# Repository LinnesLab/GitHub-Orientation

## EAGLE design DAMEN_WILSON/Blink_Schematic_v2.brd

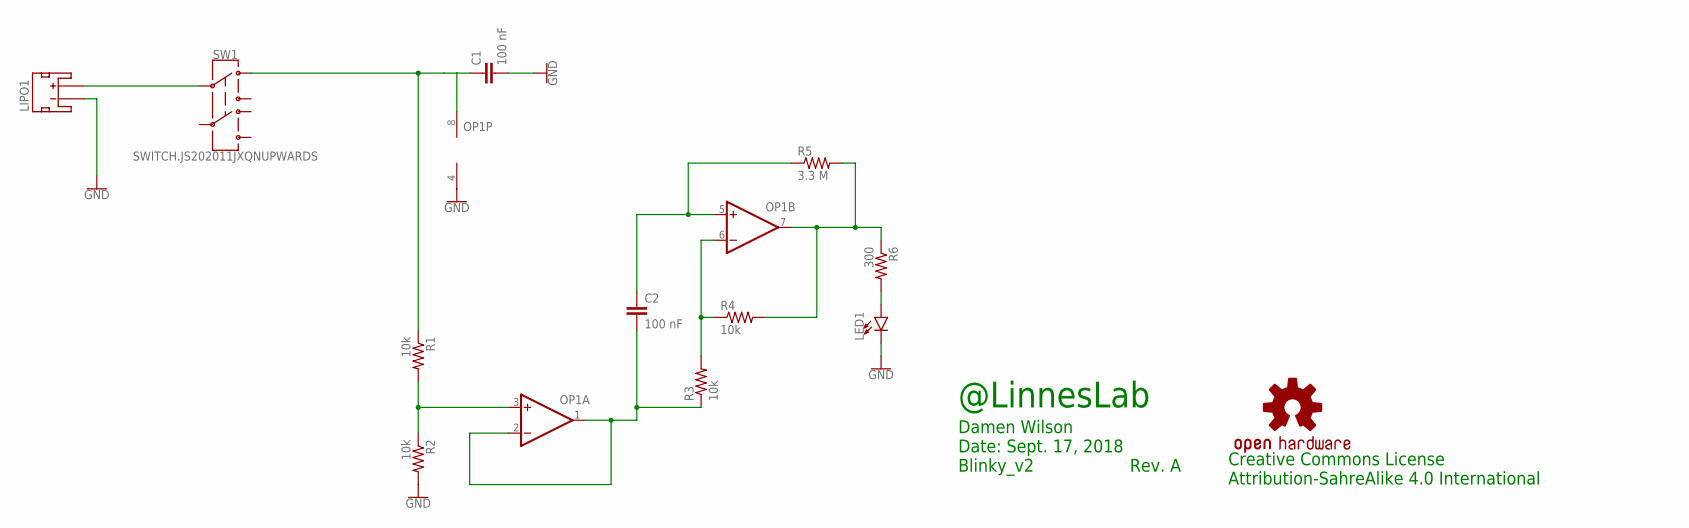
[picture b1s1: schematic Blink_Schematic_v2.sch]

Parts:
C1, C2: 100 nF; C0402
LED1: LED0603; LED-0603
LIPO1: JST_2MM_MALE; JST-2-SMD
LOGO1: OSHW-LOGOL; OSHW-LOGO-L
OP1: OP-DUALRM; MSOP08
R1, R2, R3, R4: 10k; R0402
R5: 3.3 M; R0402
R6: 300; R0402
SW1: SWITCH.JS202011JXQNUPWARDS; SWITCH.00

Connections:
GND: C1.2, LED1.C, LIPO1.1 (-), OP1.4 (V-), R2.2
unnamed: LIPO1.2 (+), SW1.2
unnamed: C1.1, OP1.8 (V+), R1.1, SW1.1
unnamed: OP1.3 (+IN), R1.2, R2.1
unnamed: C2.2, OP1.1 (OUT), OP1.2 (-IN), R3.1
unnamed: C2.1, OP1.5 (+IN), R5.1
unnamed: OP1.6 (-IN), R3.2, R4.1
unnamed: OP1.7 (OUT), R4.2, R5.2, R6.1
unnamed: LED1.A, R6.2

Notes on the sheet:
@LinnesLab
Damen Wilson Date: Sept. 17, 2018 Blinky_v2 Rev. A
Creative Commons License Attribution-SahreAlike 4.0 International

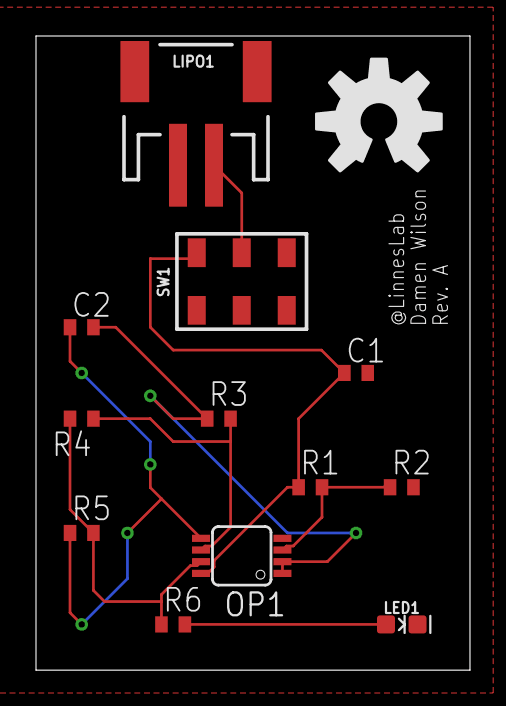
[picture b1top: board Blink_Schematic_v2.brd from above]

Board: 2 copper layers, 24.1 x 35.2 mm, 13 parts (0 on the bottom side), 9 nets.

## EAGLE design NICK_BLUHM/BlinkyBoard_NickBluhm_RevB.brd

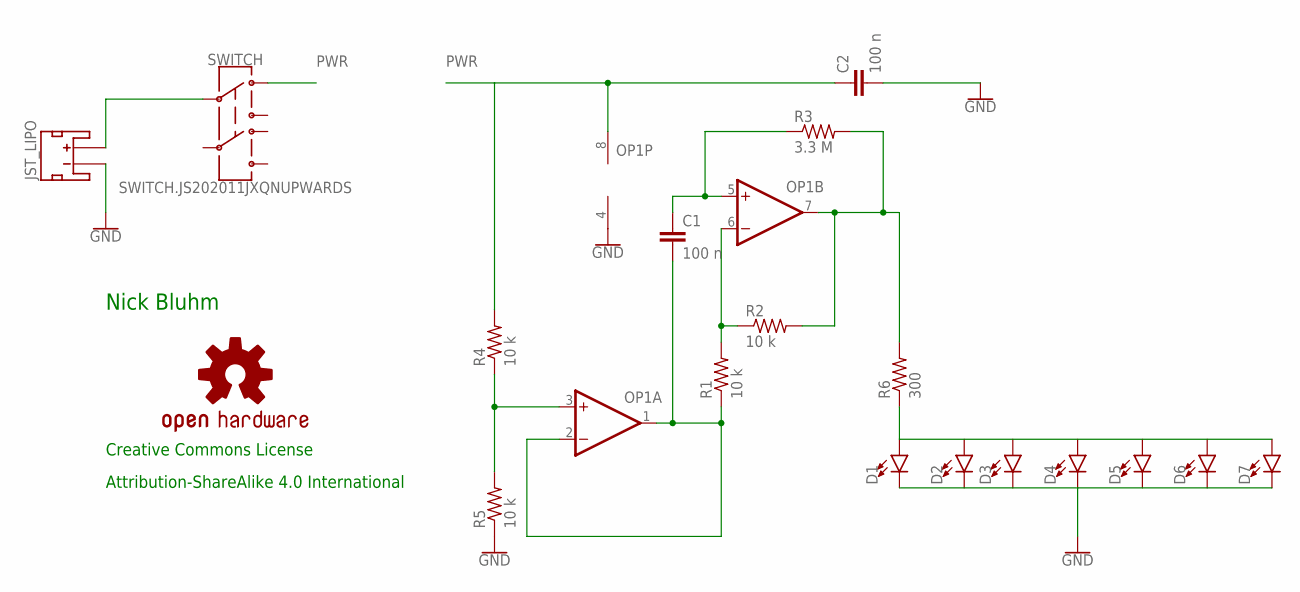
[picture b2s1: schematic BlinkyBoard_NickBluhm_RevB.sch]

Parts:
C1, C2: 100 n; C0402
D1, D2, D3, D4, D5, D6, D7: LED0603; LED-0603
JST_LIPO: 3.7 V; JST-2-SMD
LOGO1: OSHW-LOGOL-COPPER; OSHW-LOGO-L_COPPER
OP1: OP-DUALRM; MSOP08
R1, R2, R4, R5: 10 k; R0402
R3: 3.3 M; R0402
R6: 300; R0402
SWITCH: SWITCH.JS202011JXQNUPWARDS; SWITCH.00
U$5: LINNES.LAB.LOGO

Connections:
GND: C2.2, D1.C, D7.C, JST_LIPO.1 (-), OP1.4 (V-), R5.1
unnamed: JST_LIPO.2 (+), SWITCH.2
unnamed: OP1.3 (+IN), R4.1, R5.2
unnamed: C1.2, OP1.1 (OUT), OP1.2 (-IN), R1.1
unnamed: OP1.6 (-IN), R1.2, R2.1
unnamed: C1.1, OP1.5 (+IN), R3.1
unnamed: OP1.7 (OUT), R2.2, R3.2, R6.2
unnamed: D1.A, D7.A, R6.1
PWR: C2.1, OP1.8 (V+), R4.2, SWITCH.1

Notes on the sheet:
Nick Bluhm
Creative Commons License
Attribution-ShareAlike 4.0 International

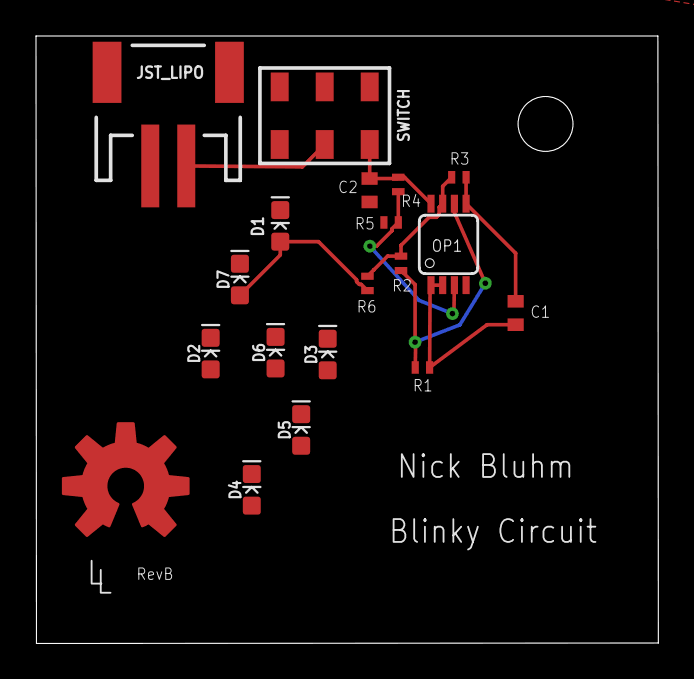
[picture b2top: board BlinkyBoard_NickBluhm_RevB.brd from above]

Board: 2 copper layers, 34.6 x 33.7 mm, 20 parts (0 on the bottom side), 9 nets.

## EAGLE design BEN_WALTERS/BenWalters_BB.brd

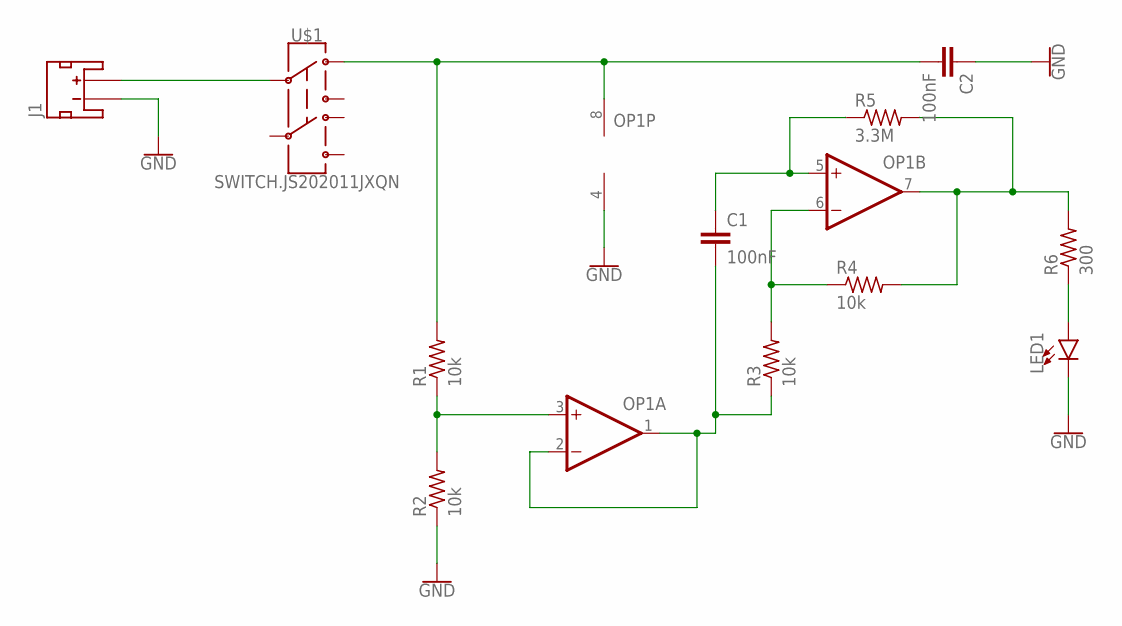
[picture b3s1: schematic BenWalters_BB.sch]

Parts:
C1, C2: 100nF; C0805
J1: 3.7V; JST-2-SMD
LED1: LED3MM; LED_3MM
OP1: OP-DUALRM; MSOP08
R1, R2, R3, R4: 10k; R0805
R5: 3.3M; R0805
R6: 300; R0805
U$1: SWITCH.JS202011JXQN; SWITCH.00.THT

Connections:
GND: C2.1, J1.1 (-), LED1.K (C), OP1.4 (V-), R2.1
unnamed: J1.2 (+), U$1.2
unnamed: C2.2, OP1.8 (V+), R1.2, U$1.1
unnamed: OP1.3 (+IN), R1.1, R2.2
unnamed: C1.2, OP1.1 (OUT), OP1.2 (-IN), R3.1
unnamed: OP1.6 (-IN), R3.2, R4.1
unnamed: C1.1, OP1.5 (+IN), R5.1
unnamed: OP1.7 (OUT), R4.2, R5.2, R6.2
unnamed: LED1.A, R6.1

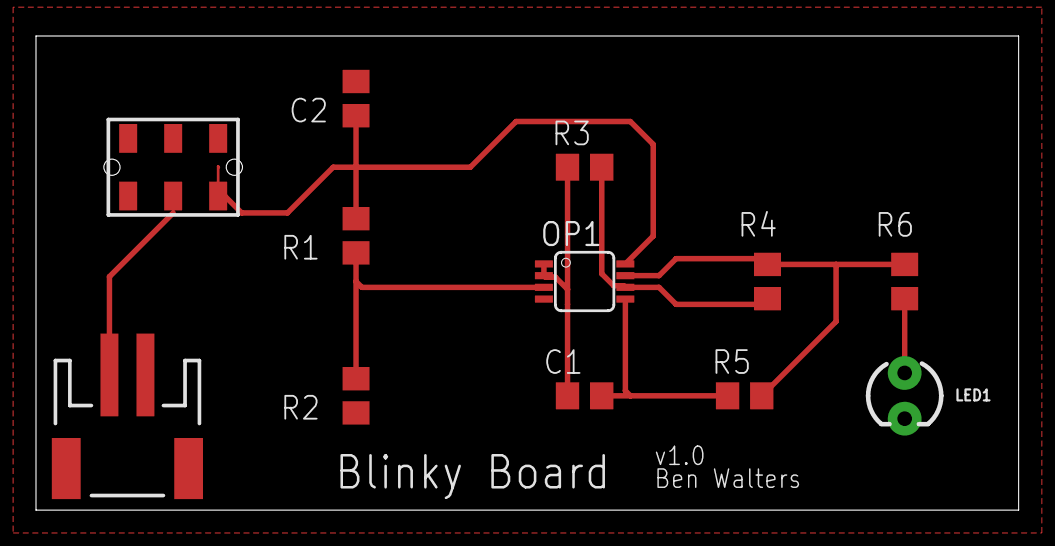
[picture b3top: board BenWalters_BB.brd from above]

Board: 2 copper layers, 54.6 x 26.3 mm, 12 parts (0 on the bottom side), 9 nets.

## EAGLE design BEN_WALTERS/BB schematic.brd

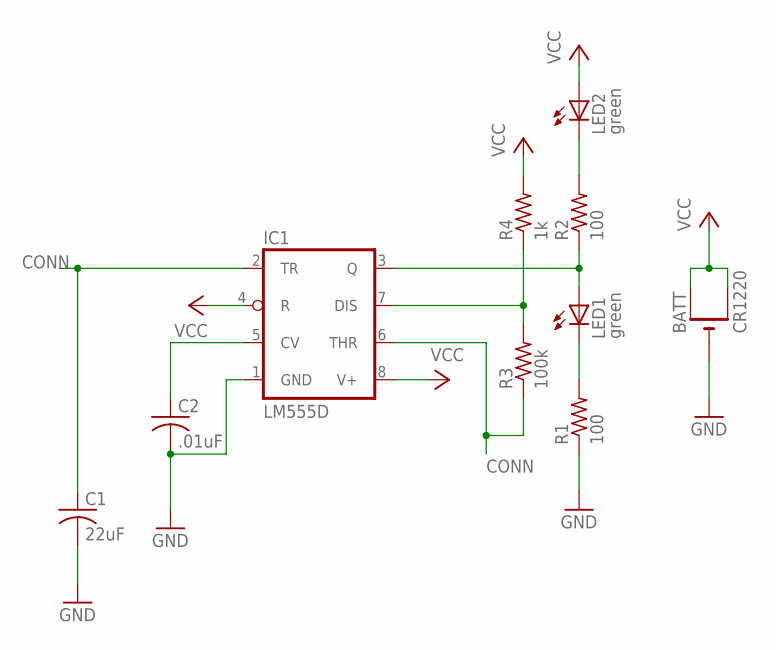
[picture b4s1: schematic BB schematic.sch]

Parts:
BATT: CR1220; CR1220-SMD; MPN 3080
C1: 22uF; C0805; MPN C2012X5R0J226M125AC
C2: .01uF; C0805; MPN MC0805B103M500CT
IC1: LM555D; SO08; MPN TLC555ID
LED1, LED2: green; CHIPLED_0805; MPN 5988170107F
R1, R2: 100; R0805; MPN MCTF0805BTC1000
R3: 100k; R0805; MPN CRCW0805100KFKTA
R4: 1k; R0805; MPN MCTF0805BTC1001

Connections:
CONN: C1.1, IC1.2 (TR), IC1.6 (THR), R3.1
GND: BATT.-, C1.2, C2.2, IC1.1 (GND), R1.1
unnamed: LED2.C, R2.2
unnamed: IC1.3 (Q), LED1.A, R2.1
unnamed: LED1.C, R1.2
unnamed: IC1.7 (DIS), R3.2, R4.1
unnamed: C2.1, IC1.5 (CV)
VCC: BATT.+$1 (+), BATT.+$2 (+1), IC1.4 (R), IC1.8 (V+), LED2.A, R4.2

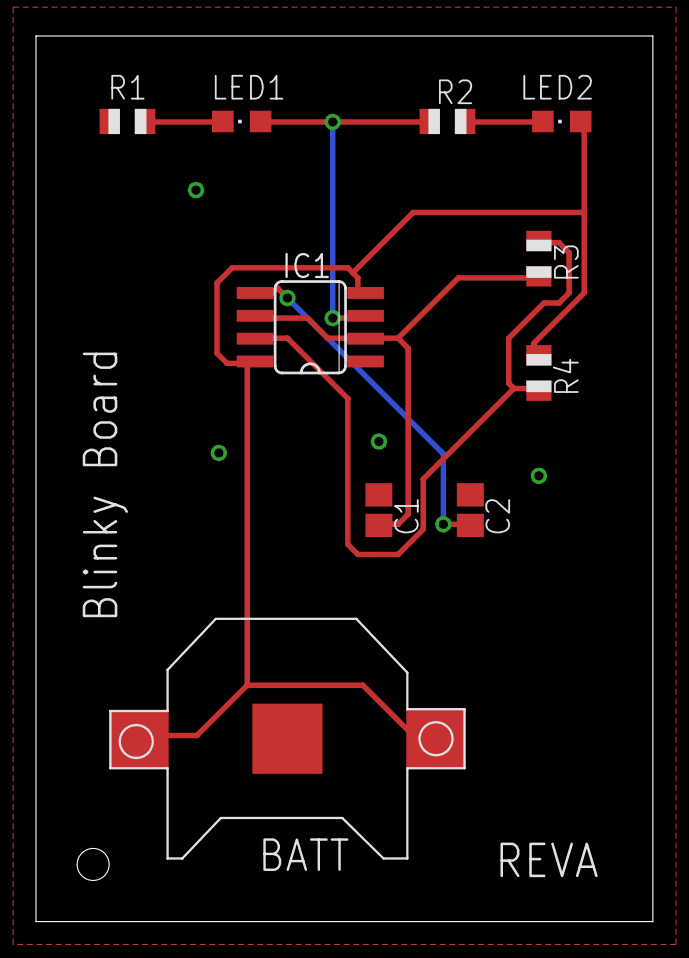
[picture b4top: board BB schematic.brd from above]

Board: 2 copper layers, 34.3 x 49.2 mm, 10 parts (0 on the bottom side), 8 nets.

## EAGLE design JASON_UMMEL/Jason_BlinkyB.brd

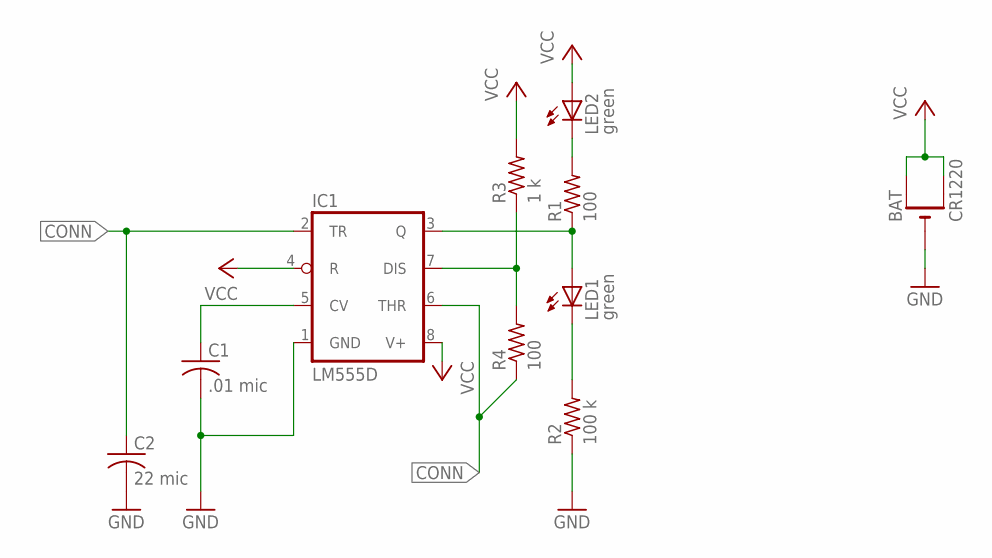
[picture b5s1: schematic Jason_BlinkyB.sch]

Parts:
BAT: CR1220; CR1220-SMD; MPN 3080
C1: .01 mic; C0805; MPN C0805C103K5RACTU
C2: 22 mic; C0805; MPN TL8W9226M010C
IC1: LM555D; SO08; MPN TLC555CD.
LED1, LED2: green; CHIPLED_0805; MPN 150080GS75000
R1, R4: 100; R0805; MPN CR0805-JW-101ELF
R2: 100 k; R0805; MPN MC01W08055100K
R3: 1 k; R0805; MPN CRCW08051K00FKTA

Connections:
CONN: C2.1, IC1.2 (TR), IC1.6 (THR), R4.1
GND: BAT.-, C1.2, C2.2, IC1.1 (GND), R2.1
unnamed: LED2.C, R1.2
unnamed: IC1.3 (Q), LED1.A, R1.1
unnamed: LED1.C, R2.2
unnamed: IC1.7 (DIS), R3.1, R4.2
unnamed: C1.1, IC1.5 (CV)
VCC: BAT.+$1 (+), BAT.+$2 (+1), IC1.4 (R), IC1.8 (V+), LED2.A, R3.2

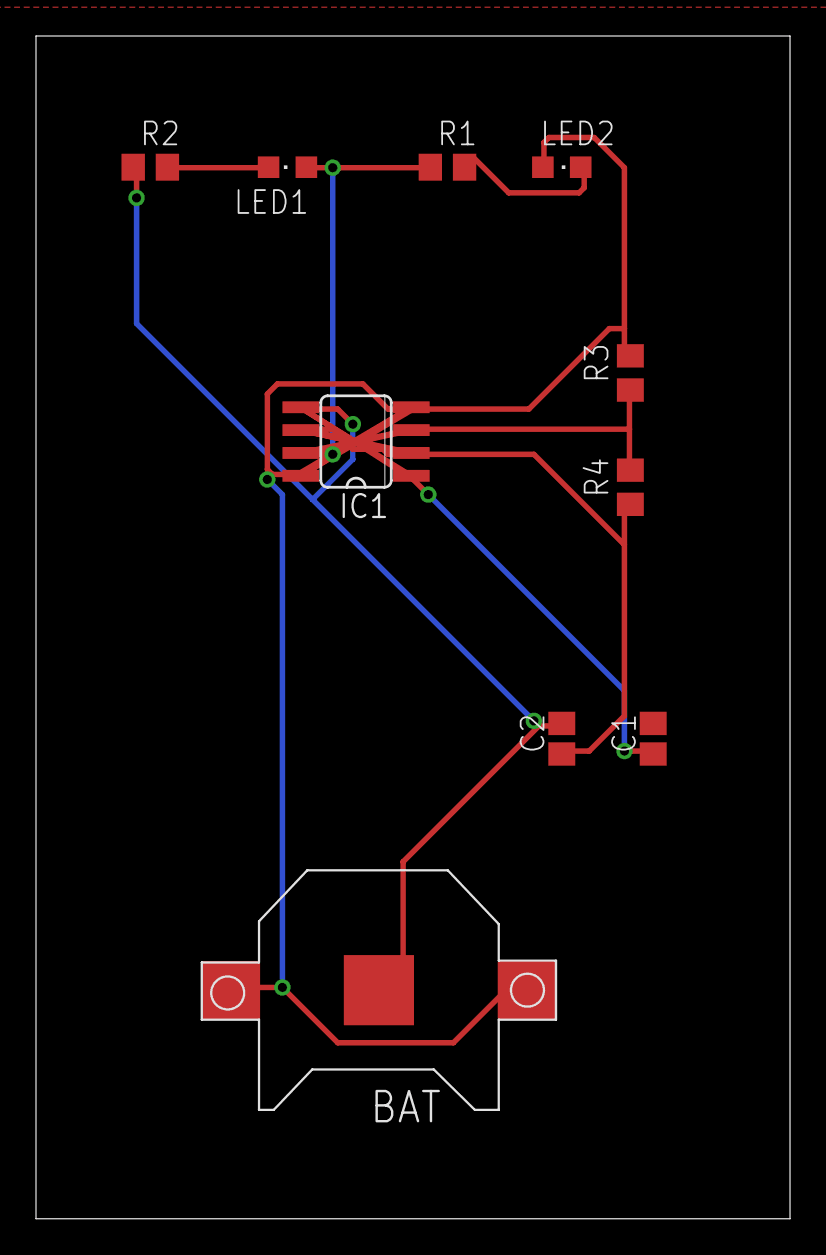
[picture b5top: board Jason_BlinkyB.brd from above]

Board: 2 copper layers, 41.9 x 65.7 mm, 10 parts (0 on the bottom side), 8 nets.

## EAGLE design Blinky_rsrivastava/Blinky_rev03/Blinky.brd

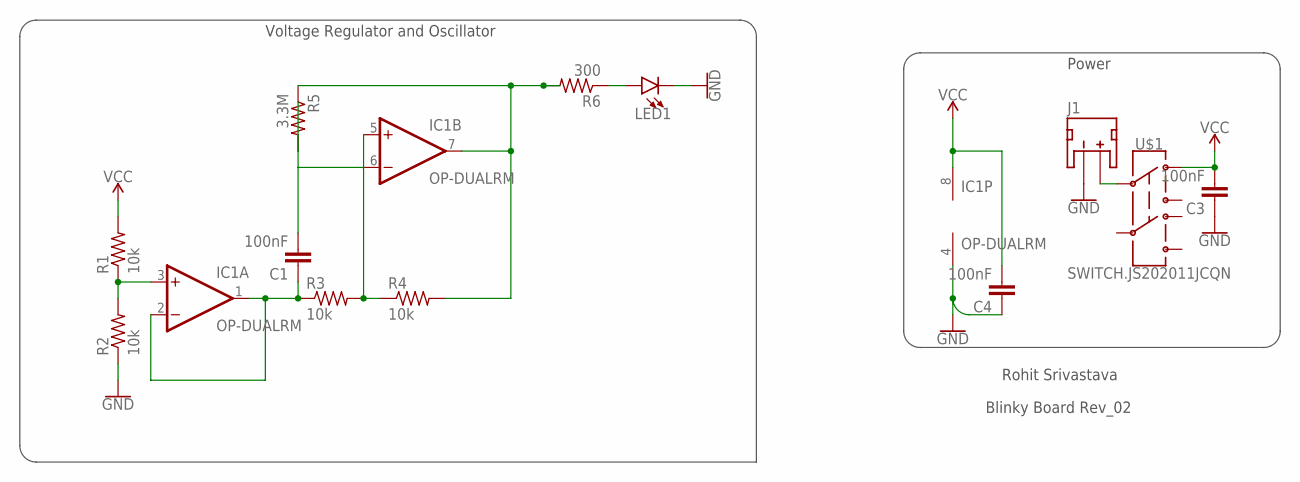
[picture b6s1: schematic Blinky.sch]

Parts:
C1, C3, C4: 100nF; C0402
IC1: OP-DUALRM; MSOP08
J1: JST_2MM_MALE; JST-2-SMD
LED1: LED0603; LED-0603
R1, R2, R3, R4: 10k; R0402
R5: 3.3M; R0402
R6: 300; R0402
U$1: SWITCH.JS202011JCQN; SWITCH.00

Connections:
GND: C3.1, C4.1, IC1.4 (V-), J1.1 (-), LED1.C, R2.1
unnamed: J1.2 (+), U$1.2
unnamed: C1.1, IC1.1 (OUT), IC1.2 (-IN), R3.1
unnamed: IC1.5 (+IN), R3.2, R4.1
unnamed: C1.2, IC1.6 (-IN), R5.2
unnamed: IC1.3 (+IN), R1.1, R2.2
unnamed: IC1.7 (OUT), R4.2, R5.1, R6.2
unnamed: LED1.A, R6.1
VCC: C3.2, C4.2, IC1.8 (V+), R1.2, U$1.1

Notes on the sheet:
Power
Voltage Regulator and Oscillator
Rohit Srivastava
Blinky Board Rev_02

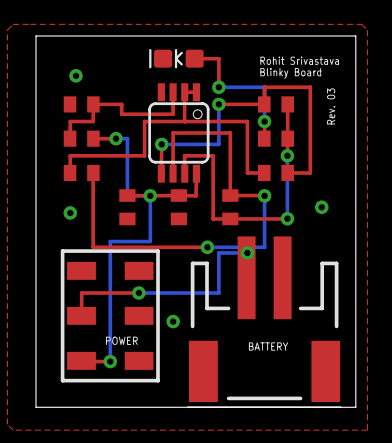
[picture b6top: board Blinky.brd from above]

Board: 2 copper layers, 17.8 x 20.6 mm, 13 parts (0 on the bottom side), 9 nets.

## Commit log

2017-06-15 Added first itteration of orientation LED circuit
2017-06-18 updates and removing excessive files
2017-06-20 Push second revision
2017-06-28 Added 3rd revision, manually routed
2017-09-17 Added my generic JASON_UMMEL file
2017-09-17 added my sketch and board to my folder
2018-06-12 added NICK_BLUHM.txt
2018-06-12 added txt file to branch
2018-06-22 Adding a Folder to store my files in
2018-06-22 I moved this file into my folder named NICK_BLUHM
2018-06-22 I moved this file to my folder named NICK_BLUHM
2018-06-22 Adding my Blinky Board board file
2018-06-22 Adding my blinky board schematic file
2018-06-23 First text file with name
2018-06-23 Second txt with name
2018-06-23 Added blinky board sketch and board
2018-06-23 moved text files
2018-06-23 removed unecessary txt files
2018-06-23 Remove extra txt files
2018-06-28 Updated Blinky Board
2018-07-10 Adding RevB files for blinky board
2018-09-01 Added for test
2018-09-01 for branch test
2018-09-01 Blinky Board files
2018-09-18 New revision for board
2018-10-16 Arduino Library for on Board Led blinking
2021-04-01 added a text file for test
2021-04-01 this is my branch file test
2021-04-01 added a gitignore file
2021-04-01 removed large, unnecessary file
2021-04-01 this is a test
